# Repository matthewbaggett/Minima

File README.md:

# Minima
Experimental Basic "computer-like" hardware.

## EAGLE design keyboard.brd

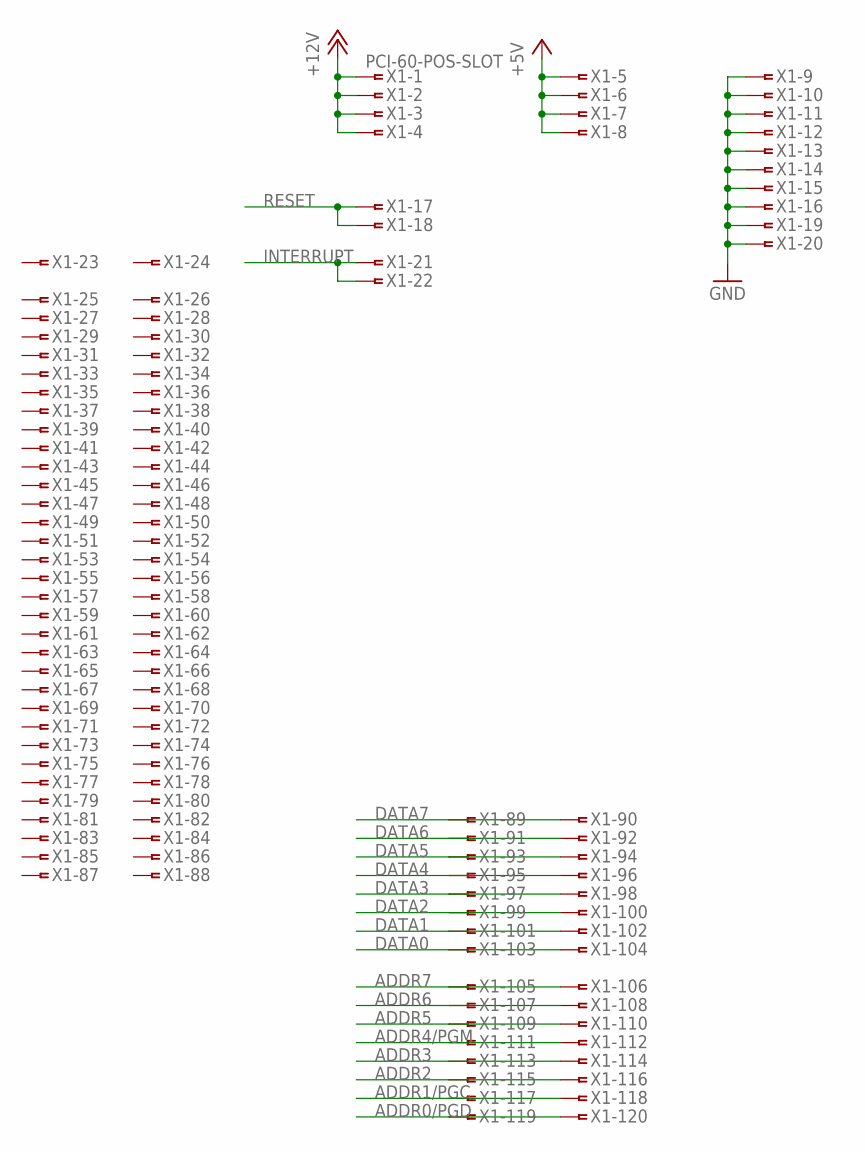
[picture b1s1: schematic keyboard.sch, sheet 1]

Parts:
X1: PCI-60-POS-SLOT; PCI-SLOT-60

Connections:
+5V: X1.5, X1.6, X1.7, X1.8; also elsewhere on the board
+12V: X1.1, X1.2, X1.3, X1.4
ADDR0/PGD: X1.119, X1.120; also elsewhere on the board
ADDR1/PGC: X1.117, X1.118; also elsewhere on the board
ADDR2: X1.115, X1.116; also elsewhere on the board
ADDR3: X1.113, X1.114; also elsewhere on the board
ADDR4/PGM: X1.111, X1.112; also elsewhere on the board
ADDR5: X1.109, X1.110; also elsewhere on the board
ADDR6: X1.107, X1.108; also elsewhere on the board
ADDR7: X1.105, X1.106; also elsewhere on the board
DATA0: X1.103, X1.104; also elsewhere on the board
DATA1: X1.101, X1.102; also elsewhere on the board
DATA2: X1.99, X1.100; also elsewhere on the board
DATA3: X1.97, X1.98; also elsewhere on the board
DATA4: X1.95, X1.96; also elsewhere on the board
DATA5: X1.93, X1.94; also elsewhere on the board
DATA6: X1.91, X1.92; also elsewhere on the board
DATA7: X1.89, X1.90; also elsewhere on the board
GND: X1.9, X1.10, X1.11, X1.12, X1.13, X1.14, X1.15, X1.16, X1.19, X1.20; also elsewhere on the board
INTERRUPT: X1.21, X1.22; also elsewhere on the board
RESET: X1.17, X1.18; also elsewhere on the board

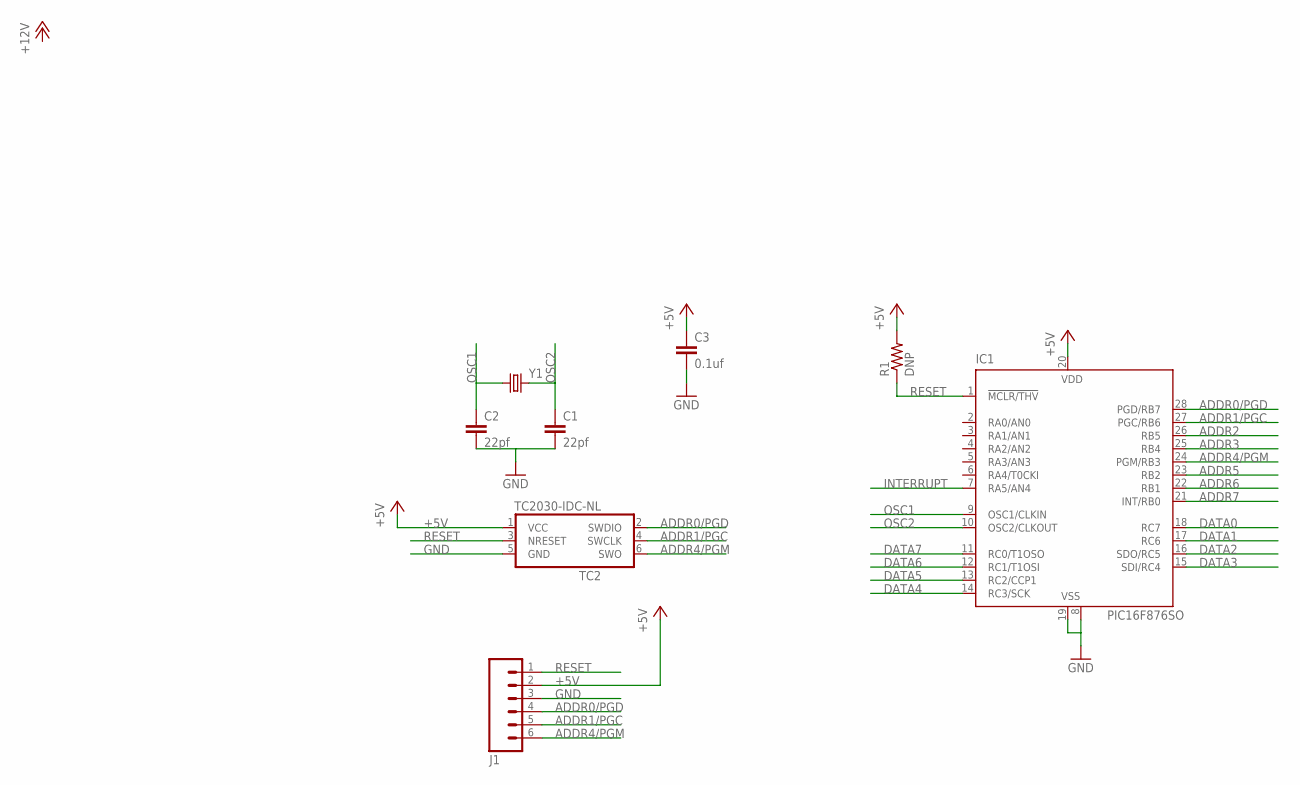
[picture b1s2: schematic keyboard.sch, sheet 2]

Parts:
C1, C2: 22pf; 1206
C3: 0.1uf; 1206
IC1: PIC16F876SO; SO28W
J1: M06POLAR_LOCK; MOLEX-1X6_LOCK
R1: DNP; 1206
TC2: TC2030-IDC-NL
Y1: CRYSTALSMD; HC49UP

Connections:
+5V: C3.1, IC1.20 (VDD), J1.2, R1.2, TC2.1 (VCC); also elsewhere on the board
ADDR0/PGD: IC1.28 (PGD/RB7), J1.4, TC2.2 (SWDIO); also elsewhere on the board
ADDR1/PGC: IC1.27 (PGC/RB6), J1.5, TC2.4 (SWCLK); also elsewhere on the board
ADDR2: IC1.26 (RB5); also elsewhere on the board
ADDR3: IC1.25 (RB4); also elsewhere on the board
ADDR4/PGM: IC1.24 (PGM/RB3), J1.6, TC2.6 (SWO); also elsewhere on the board
ADDR5: IC1.23 (RB2); also elsewhere on the board
ADDR6: IC1.22 (RB1); also elsewhere on the board
ADDR7: IC1.21 (INT/RB0); also elsewhere on the board
DATA0: IC1.18 (RC7); also elsewhere on the board
DATA1: IC1.17 (RC6); also elsewhere on the board
DATA2: IC1.16 (SDO/RC5); also elsewhere on the board
DATA3: IC1.15 (SDI/RC4); also elsewhere on the board
DATA4: IC1.14 (RC3/SCK); also elsewhere on the board
DATA5: IC1.13 (RC2/CCP1); also elsewhere on the board
DATA6: IC1.12 (RC1/T1OSI); also elsewhere on the board
DATA7: IC1.11 (RC0/T1OSO); also elsewhere on the board
GND: C1.2, C2.2, C3.2, IC1.8 (VSS), IC1.19 (VSS), J1.3, TC2.5 (GND); also elsewhere on the board
INTERRUPT: IC1.7 (RA5/AN4); also elsewhere on the board
OSC1: C2.1, IC1.9 (OSC1/CLKIN), Y1.1
OSC2: C1.1, IC1.10 (OSC2/CLKOUT), Y1.2
RESET: IC1.1 (!MCLR/THV), J1.1, R1.1, TC2.3 (NRESET); also elsewhere on the board

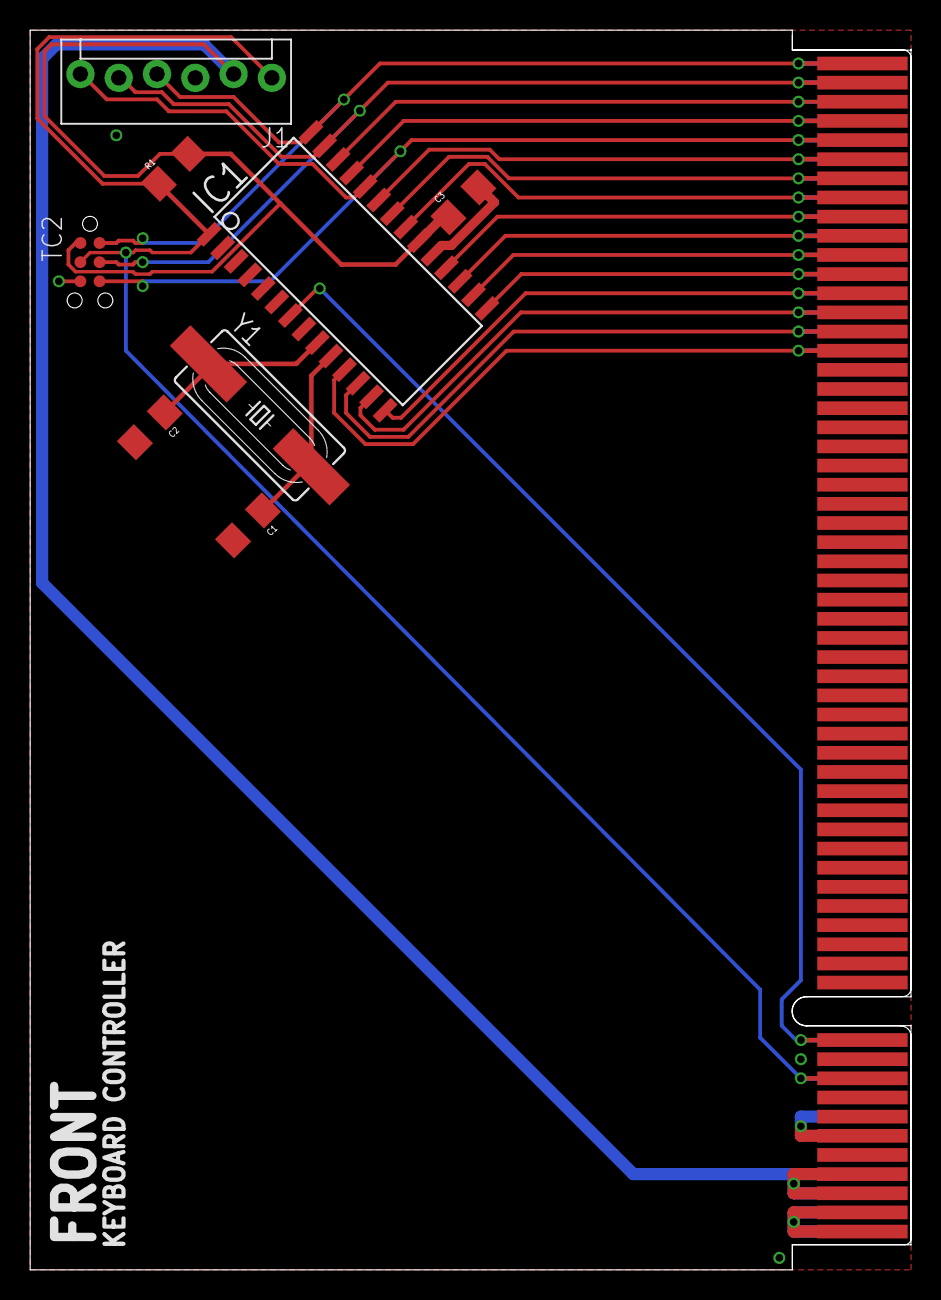
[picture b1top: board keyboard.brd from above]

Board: 2 copper layers, 58.4 x 82.2 mm, 9 parts (0 on the bottom side), 23 nets.

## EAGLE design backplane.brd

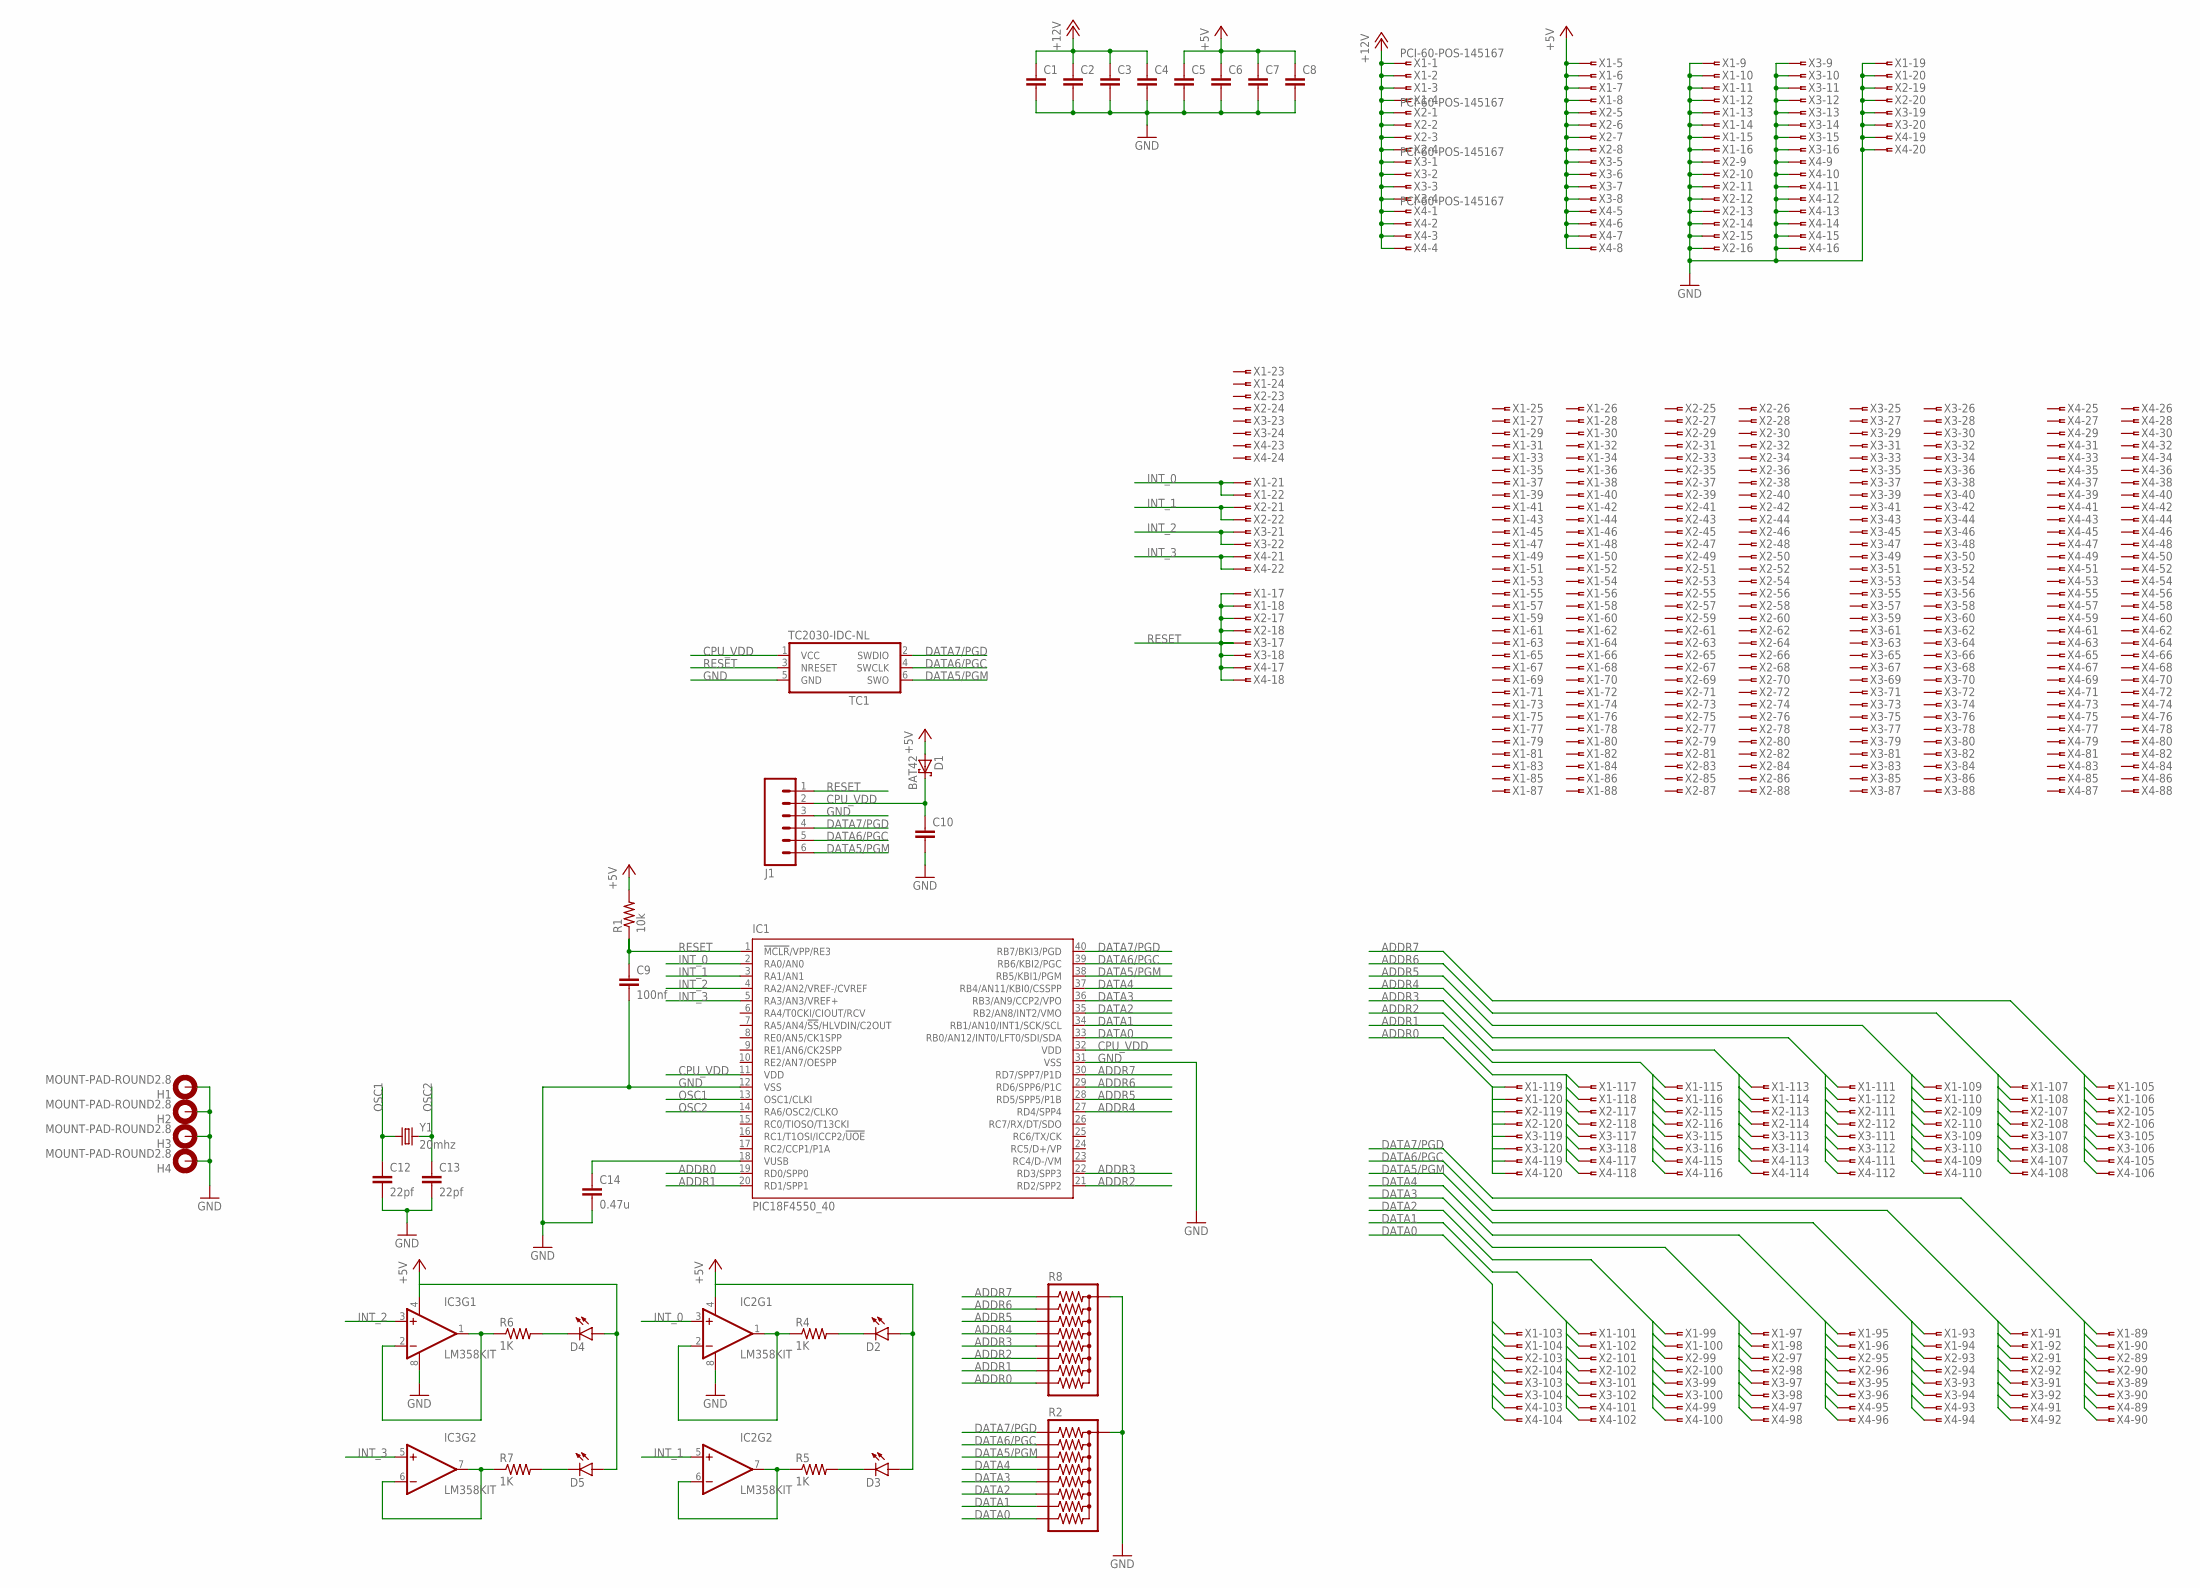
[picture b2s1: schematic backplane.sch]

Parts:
C1, C2, C3, C4, C5, C6, C7, C8, C10: 0.1UF-50V-20%(PTH)KIT-EZ; CAP-PTH-SMALL-KIT
C9: 100nf; CAP-PTH-SMALL-KIT
C12, C13: 22pf; CAP-PTH-SMALL-KIT
C14: 0.47u; CAP-PTH-SMALL-KIT
D1: BAT42; DO35-10
D2, D3, D4, D5: LED3MM
H1, H2, H3, H4: MOUNT-PAD-ROUND2.8; 2,8-PAD
IC1: PIC18F4550_40; DIL40
IC2, IC3: LM358KIT; DIP08-KIT
J1: M06POLAR_LOCK; MOLEX-1X6_LOCK
R1: 10k; AXIAL-0.3EZ
R2, R8: RPACK-BUSSED-8-SIP-PTH-8; RPACK-SIP-PTH-8
R4, R5, R6, R7: 1K; AXIAL-0.1EZ
TC1: TC2030-IDC-NL
X1, X2, X3, X4: PCI-60-POS-145167; 145167-2
Y1: 20mhz; HC49U-V

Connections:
+5V: C5.1, C6.1, C7.1, C8.1, D1.A, D2.A, D3.A, D4.A, D5.A, IC2.4 (V-), IC3.4 (V-), R1.P$2 (2), X1.5, X1.6, X1.7, X1.8, X2.5, X2.6, X2.7, X2.8, X3.5, X3.6, X3.7, X3.8, X4.5, X4.6, X4.7, X4.8
+12V: C1.1, C2.1, C3.1, C4.1, X1.1, X1.2, X1.3, X1.4, X2.1, X2.2, X2.3, X2.4, X3.1, X3.2, X3.3, X3.4, X4.1, X4.2, X4.3, X4.4
ADDR0: IC1.19 (RD0/SPP0), R8.P$9 (9), X1.119, X1.120, X2.119, X2.120, X3.119, X3.120, X4.119, X4.120
ADDR1: IC1.20 (RD1/SPP1), R8.P$8 (8), X1.117, X1.118, X2.117, X2.118, X3.117, X3.118, X4.117, X4.118
ADDR2: IC1.21 (RD2/SPP2), R8.P$7 (7), X1.115, X1.116, X2.115, X2.116, X3.115, X3.116, X4.115, X4.116
ADDR3: IC1.22 (RD3/SPP3), R8.P$6 (6), X1.113, X1.114, X2.113, X2.114, X3.113, X3.114, X4.113, X4.114
ADDR4: IC1.27 (RD4/SPP4), R8.P$5 (5), X1.111, X1.112, X2.111, X2.112, X3.111, X3.112, X4.111, X4.112
ADDR5: IC1.28 (RD5/SPP5/P1B), R8.P$4 (4), X1.109, X1.110, X2.109, X2.110, X3.109, X3.110, X4.109, X4.110
ADDR6: IC1.29 (RD6/SPP6/P1C), R8.P$3 (3), X1.107, X1.108, X2.107, X2.108, X3.107, X3.108, X4.107, X4.108
ADDR7: IC1.30 (RD7/SPP7/P1D), R8.P$2 (2), X1.105, X1.106, X2.105, X2.106, X3.105, X3.106, X4.105, X4.106
CPU_VDD: C10.1, D1.C, IC1.11 (VDD), IC1.32 (VDD), J1.2, TC1.1 (VCC)
DATA0: IC1.33 (RB0/AN12/INT0/LFT0/SDI/SDA), R2.P$9 (9), X1.103, X1.104, X2.103, X2.104, X3.103, X3.104, X4.103, X4.104
DATA1: IC1.34 (RB1/AN10/INT1/SCK/SCL), R2.P$8 (8), X1.101, X1.102, X2.101, X2.102, X3.101, X3.102, X4.101, X4.102
DATA2: IC1.35 (RB2/AN8/INT2/VMO), R2.P$7 (7), X1.99, X1.100, X2.99, X2.100, X3.99, X3.100, X4.99, X4.100
DATA3: IC1.36 (RB3/AN9/CCP2/VPO), R2.P$6 (6), X1.97, X1.98, X2.97, X2.98, X3.97, X3.98, X4.97, X4.98
DATA4: IC1.37 (RB4/AN11/KBI0/CSSPP), R2.P$5 (5), X1.95, X1.96, X2.95, X2.96, X3.95, X3.96, X4.95, X4.96
DATA5/PGM: IC1.38 (RB5/KBI1/PGM), J1.6, R2.P$4 (4), TC1.6 (SWO), X1.93, X1.94, X2.93, X2.94, X3.93, X3.94, X4.93, X4.94
DATA6/PGC: IC1.39 (RB6/KBI2/PGC), J1.5, R2.P$3 (3), TC1.4 (SWCLK), X1.91, X1.92, X2.91, X2.92, X3.91, X3.92, X4.91, X4.92
DATA7/PGD: IC1.40 (RB7/BKI3/PGD), J1.4, R2.P$2 (2), TC1.2 (SWDIO), X1.89, X1.90, X2.89, X2.90, X3.89, X3.90, X4.89, X4.90
GND: C1.2, C2.2, C3.2, C4.2, C5.2, C6.2, C7.2, C8.2, C9.2, C10.2, C12.2, C13.2, C14.2, H1.B2,8, H2.B2,8, H3.B2,8, H4.B2,8, IC1.12 (VSS), IC1.31 (VSS), IC2.8 (V+), IC3.8 (V+), J1.3, R2.P$1 (1), R8.P$1 (1), TC1.5 (GND), X1.9, X1.10, X1.11, X1.12, X1.13, X1.14, X1.15, X1.16, X1.19, X1.20, X2.9, X2.10, X2.11, X2.12, X2.13, X2.14, X2.15, X2.16, X2.19, X2.20, X3.9, X3.10, X3.11, X3.12, X3.13, X3.14, X3.15, X3.16, X3.19, X3.20, X4.9, X4.10, X4.11, X4.12, X4.13, X4.14, X4.15, X4.16, X4.19, X4.20
INT_0: IC1.2 (RA0/AN0), IC2.3 (+IN), X1.21, X1.22
INT_1: IC1.3 (RA1/AN1), IC2.5 (+IN), X2.21, X2.22
INT_2: IC1.4 (RA2/AN2/VREF-/CVREF), IC3.3 (+IN), X3.21, X3.22
INT_3: IC1.5 (RA3/AN3/VREF+), IC3.5 (+IN), X4.21, X4.22
unnamed: D2.K (C), R4.P$2 (2)
unnamed: D3.K (C), R5.P$2 (2)
unnamed: IC2.6 (-IN), IC2.7 (OUT), R5.P$1 (1)
unnamed: IC2.1 (OUT), IC2.2 (-IN), R4.P$1 (1)
unnamed: D4.K (C), R6.P$2 (2)
unnamed: D5.K (C), R7.P$2 (2)
unnamed: IC3.6 (-IN), IC3.7 (OUT), R7.P$1 (1)
unnamed: IC3.1 (OUT), IC3.2 (-IN), R6.P$1 (1)
unnamed: C14.1, IC1.18 (VUSB)
OSC1: C12.1, IC1.13 (OSC1/CLKI), Y1.1
OSC2: C13.1, IC1.14 (RA6/OSC2/CLKO), Y1.2
RESET: C9.1, IC1.1 (!MCLR!/VPP/RE3), J1.1, R1.P$1 (1), TC1.3 (NRESET), X1.17, X1.18, X2.17, X2.18, X3.17, X3.18, X4.17, X4.18

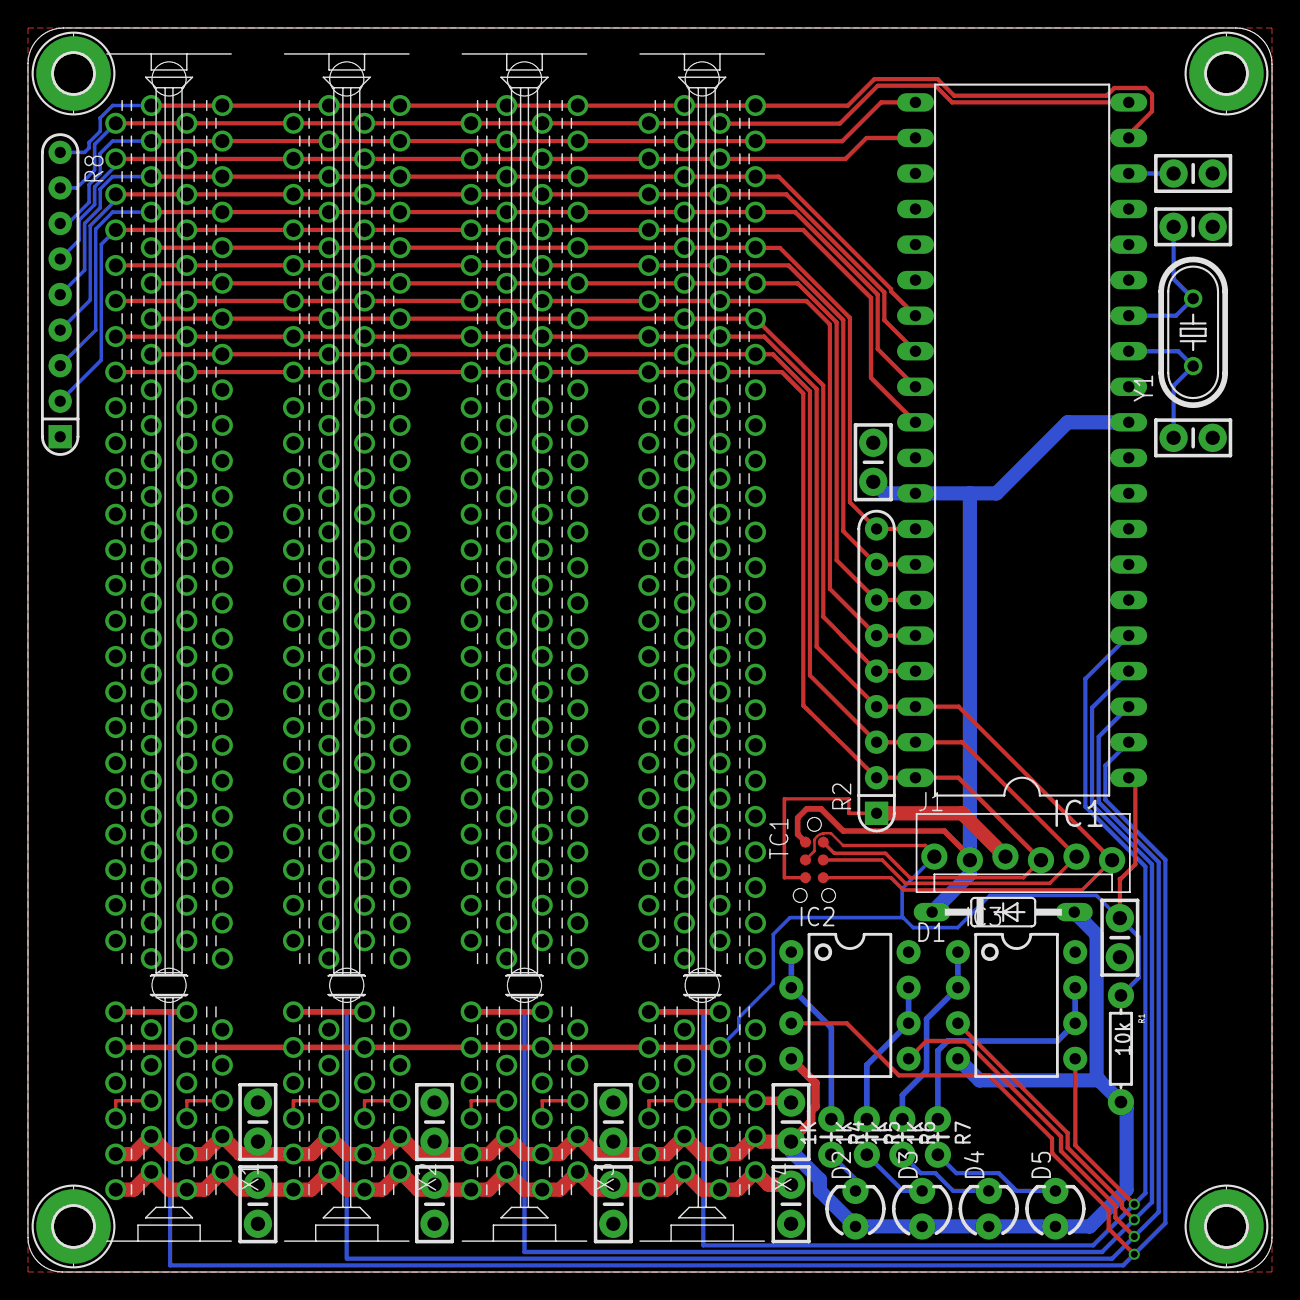
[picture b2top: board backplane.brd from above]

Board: 2 copper layers, 88.9 x 88.9 mm, 39 parts (0 on the bottom side), 36 nets.

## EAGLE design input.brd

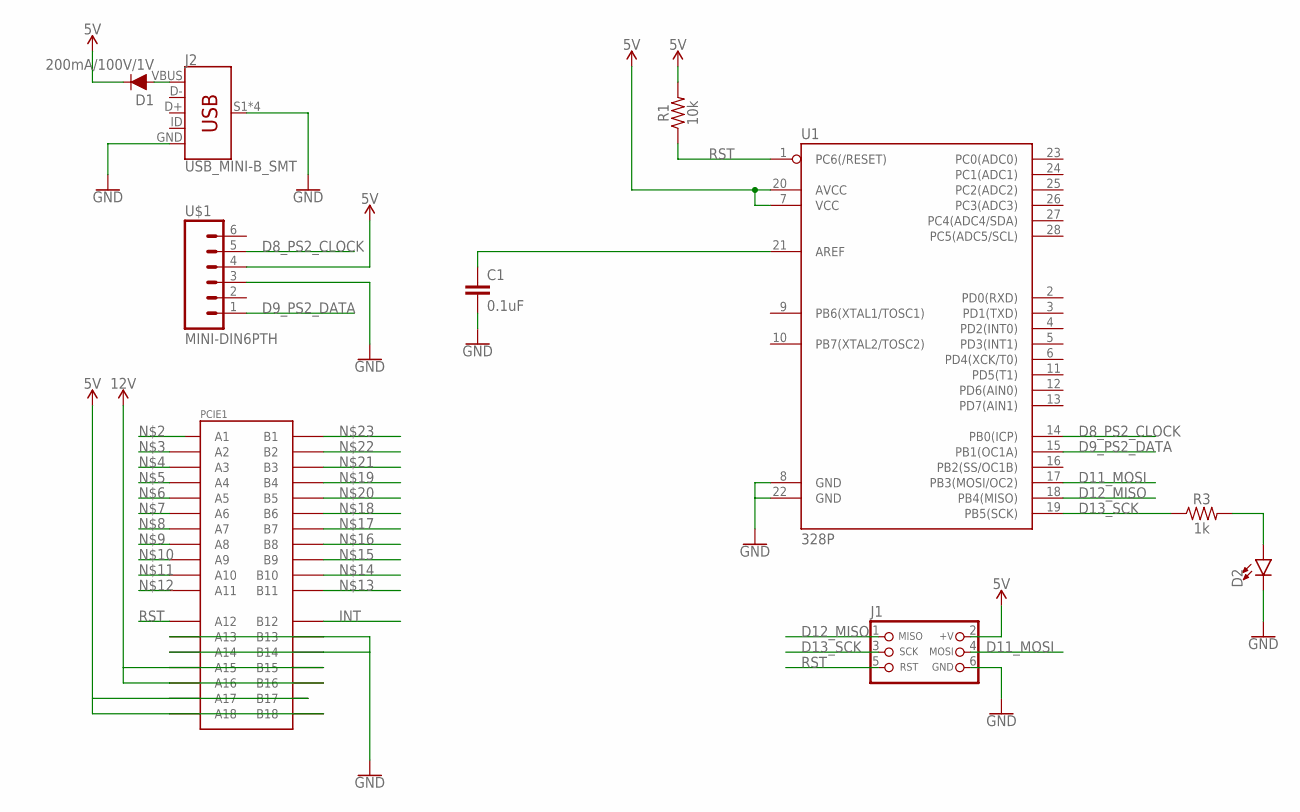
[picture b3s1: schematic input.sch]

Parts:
C1: 0.1uF; CAP-PTH-SMALL-KIT
D1: 200mA/100V/1V; DIODE-1N4148
D2: LED5MM-KIT; LED_5MM-KIT
J1: CON_HEADER_PRG_AVR_ICSP-PTH; HEADER_PRG_2X03
J2: USB_MINI-B_SMT; USB-MINIB
PCIE1: PCIE-36-EDGE
R1: 10k; AXIAL-0.3
R3: 1k; AXIAL-0.3
U1: 328P; DIP28
U$1: MINI-DIN6PTH; MINI-DIN6

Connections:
5V: D1.C, J1.2 (+V), PCIE1.A17, PCIE1.A18, PCIE1.B17, PCIE1.B18, R1.P$2 (2), U1.7 (VCC), U1.20 (AVCC), U$1.4
12V: PCIE1.A15, PCIE1.A16, PCIE1.B15, PCIE1.B16
D8_PS2_CLOCK: U1.14 (PB0(ICP)), U$1.5
D9_PS2_DATA: U1.15 (PB1(OC1A)), U$1.1
D11_MOSI: J1.4 (MOSI), U1.17 (PB3(MOSI/OC2))
D12_MISO: J1.1 (MISO), U1.18 (PB4(MISO))
D13_SCK: J1.3 (SCK), R3.P$1 (1), U1.19 (PB5(SCK))
GND: C1.2, D2.K (C), J1.6 (GND), J2.GND, J2.S1 (SHIELD), J2.S2 (SHIELD), J2.S3 (SHIELD), J2.S4 (SHIELD), PCIE1.A13, PCIE1.A14, PCIE1.B13, PCIE1.B14, U1.8 (GND), U1.22 (GND), U$1.3
INT: PCIE1.B12
unnamed: D1.A, J2.VBUS
unnamed: C1.1, U1.21 (AREF)
unnamed: D2.A, R3.P$2 (2)
RST: J1.5 (RST), PCIE1.A12, R1.P$1 (1), U1.1 (PC6(/RESET))

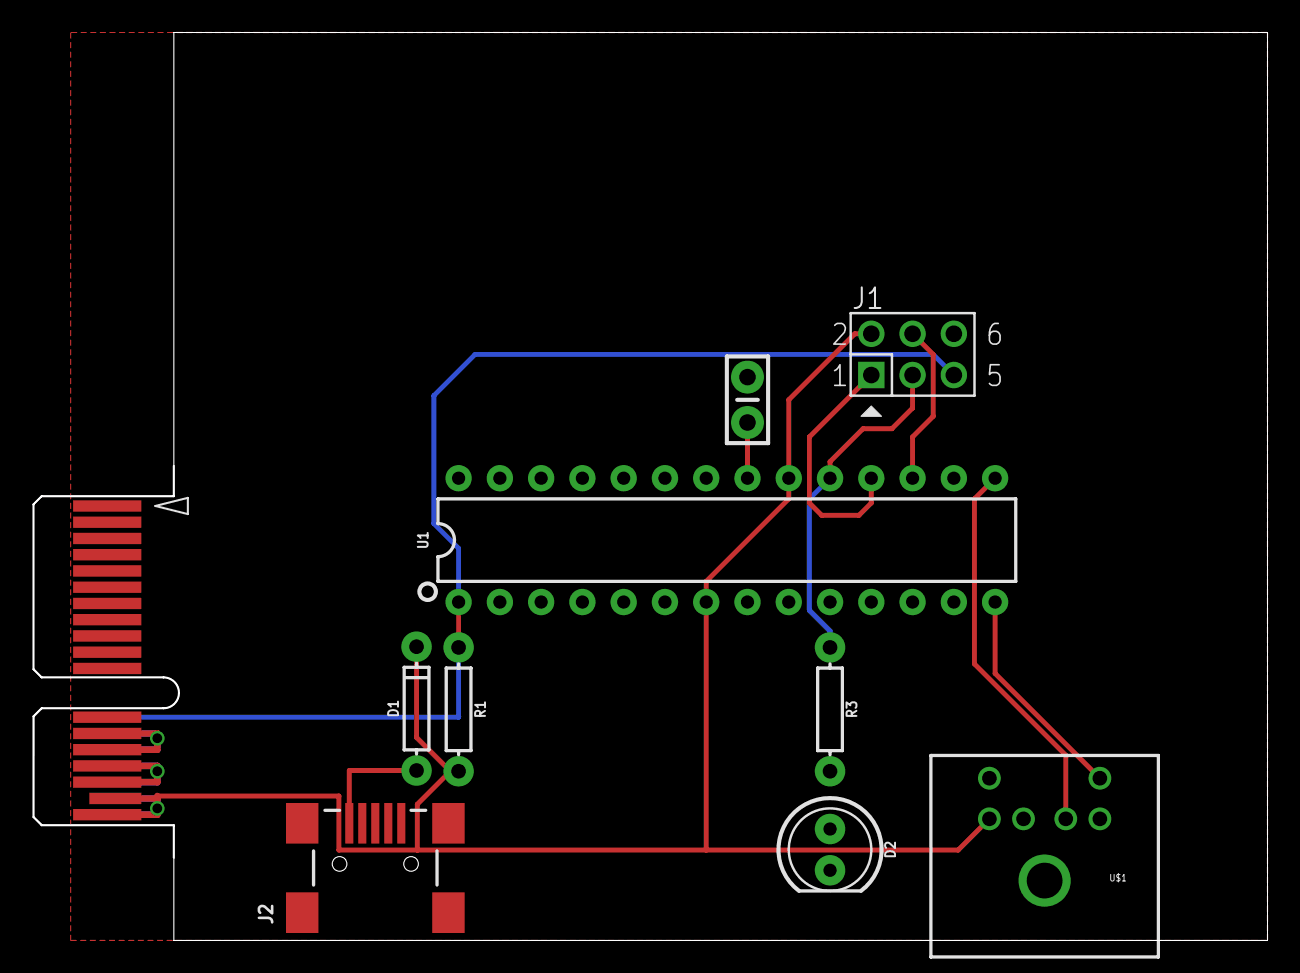
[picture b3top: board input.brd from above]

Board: 2 copper layers, 75.9 x 55.8 mm, 10 parts (0 on the bottom side), 12 nets.

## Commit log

2017-03-09 Initial crap
2017-03-10 Restandardising on the old PCI 120 way connector (reduced to 60 way).. 8 bit address bus, 8 bit data bus. PIC microcontrollers all the way, just for funzies..
2017-03-10 Unfinished keyboard controller. 16 IO lost to the interface, but I only need 2 other pins from PORTA on the '876 to talk to a keyboard.. maybe even a mouse, since I have 5 left. Maybe a status indica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

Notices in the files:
parts and their libraries:
SparkFun-Capacitors: Licensing: Creative Commons ShareAlike 4.0 International - https://creativecommons.org/licenses/by-sa/4.0
SparkFun: Licensing: CC v3.0 Share-Alike You are welcome to use this library for commercial purposes.
